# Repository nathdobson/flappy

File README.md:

# A 3d-printed Split Flap Display

This project is a redesign of David
Kingsman's [Split Flap Display](https://www.printables.com/model/69464-split-flap-display). See also the [product page](https://burntoutbakery.shop/).

## How it works

This display shows a sequence of symbols in individual 3d-printed modules. Each module contains a drum with flaps
displaying individual symbols. This is similar to a rolodex, except each symbol is split across the front of one flap
and the back of another flap. A motor rotates the drum to change from one symbol to another.

A client (e.g. [this webpage](https://flappy-7d77d.web.app/www)) sends messages to the microcontroller (MCU)
over [MQTT](https://mqtt.org/), a standardized publish/subscribe message protocol designed for IOT devices. Once the MCU
receives a message, it communicates with a series of daisy-chained motor driver circuit boards on the back of each
module. Each driver contains one shift register for controlling a unipolar stepper motor and one shift register for
reading a digital hall effect sensor. Each motor spins until a magnet on the drum activates the hall sensor, indicating
that the drum is at a particular absolute orientation. The motor then spins a specific number of steps to reach the
desired symbol.

## Prerequisites

Building this project from scratch requires a specific set of equipment and skills.

### Equipment

* Required

    * 3D printer with multi-material support (e.g. Bambu Labs A1 mini with AMS [^2]).
    * Device with a USB port capable of running Chrome.
    * [Soldering iron with temperature adjustment](https://www.amazon.com/Soldering-Digital-Welding-Portable-Electric/dp/B08R3515SF?th=1)
      for assembling boards and pushing Ruthex inserts into 3D printed parts.
    * Wire cutters
    * Wire strippers
    * Pliers
    * Allen wrenches

* Recommended

    * ["Dupont" crimping tool](https://www.amazon.com/IWISS-SN-28B-Crimping-AWG28-18-Dupont/dp/B00OMM4YUY?th=1) for
      assembling cables.
    * Multimeter for basic connection and voltage tests.

* Potentially useful
    * Laptop with at least 32GB of RAM for rendering models.
    * Oscilloscope for debugging serial communications.

### Skills

* Required
    * Soldering through-hole components
    * Crimping custom cables
* Recommended
    * The Rust programming language
    * Basic embedded software development
    * Basic understanding of CAD
    * Basic 3D printing debugging skills
    * Basic digital circuit design

## Bill of Materials

| Name of Part                                                                                                                                                                        | Quantity per display | Quantity per letter | 
|-------------------------------------------------------------------------------------------------------------------------------------------------------------------------------------|----------------------|---------------------|
| [Raspberry Pi Pico 2 W MCU with headers](https://www.adafruit.com/product/6328)                                                                                                     | 1                    |                     |
| 12v power supply (at least 250mA per character)                                                                                                                                     | 1                    |                     |
| [Adafruit 12v to 5v converter](https://www.adafruit.com/product/5882)                                                                                                               | 1                    |                     |
| [Custom motor driver circuit board](https://github.com/nathdobson/flappy/tree/main/driver)                                                                                          |                      | 1                   |
| [28BYJ-48 12v motor](https://www.amazon.com/Podazz-4-Phase-5-Line-Stepper-28BYJ-48/dp/B0DCFV3C2C)                                                                                   |                      | 1                   |
| [KY-003 hall sensor module](https://www.amazon.com/Ransanx-Magnetic-KY-003-3-3V-5V-Pressure/dp/B0F32N1LHX?th=1)                                                                     |                      | 1                   |
| [PLA (background color)](https://us.store.bambulab.com/products/pla-basic-filament)                                                                                                 | ~132 g               | ~217 g              |
| [PLA (foreground/text color)](https://us.store.bambulab.com/products/pla-basic-filament)                                                                                            |                      | ~18 g               |
| [PETG](https://us.store.bambulab.com/products/petg-hf) for stacked prints (optional)                                                                                                |                      | ~30 g               |
| Ruthex M2 inserts                                                                                                                                                                   | 4                    | 8                   |
| Ruthex M3 inserts                                                                                                                                                                   | 4                    | 6 - 8               |
| [M2 x 6mm button head screws](https://www.amazon.com/dp/B0CNQXP56N?th=1)                                                                                                            | 4                    | 6                   |
| [M2 x 10mm button head screws](https://www.amazon.com/dp/B0CNQVP8CC?th=1)                                                                                                           |                      | 2                   |
| [M3 x 6mm button head screws](https://www.amazon.com/dp/B0DNMZWZZV?th=1)                                                                                                            |                      | 6                   |
| [6mm x 2mm disc magnets](https://www.amazon.com/dp/B0CZ71S57Y?ref=ppx_yo2ov_dt_b_fed_asin_title&th=1) for drum                                                                      |                      | 1                   |
| Assorted dupont crimps, housings, and pin headers                                                                                                                                   |                      |                     |
| [26 AWG UL1061 stranded wire](https://www.remingtonindustries.com/hook-up-wire/hook-up-wire-26-awg-ul1061-stranded-kit-2-color-sets-2-spool-sizes-available) for hall sensor cables |                      |                     |
| Assorted solid wire for manually soldered boards                                                                                                                                    |                      |                     |
| Assorted stranded wire for cables                                                                                                                                                   |                      |                     |

## Repository structure

The repository is divided into several hardware and software components:

* [common/](common/) A cargo workspace with utilities and configuration in use by several components
* [driver/](driver/) A KiCad PCB design for the motor driver attached to each character.
* [firmware/](firmware/) A cargo workspace with the firmware for the Raspberry Pi Pico 2 W.
* [models/](models/) A cargo crate with binaries that generate .3mf files for each 3D-printed part.
* [native-client/](native-client/) A cargo workspace with a binary for configuring the display over USB or Bluetooth.
* [spindle/](spindle/) A cargo workspace with a simple scripting language for controlling the display.
* [submodules/](submodules/) A set of git submodules with forks of dependencies.
* [submodules/patina-rs](submodules/patina-rs/) A CAD library for generating 3D meshes from SDFs (signed distance
  functions).
* [web-client](web-client/) A WASM web application for interacting with the display.

## Instructions

### Hardware

1. Download the [latest release](https://github.com/nathdobson/flappy/releases/latest).
1. Order driver PCBs with JLCPCB:
    * `driver-jlcpcb-GERBER.zip` for producing the raw boards.
    * `driver-jlcpcb-BOM.csv` for ordering parts.
    * `driver-jlcpcb-CPL.csv` for placing and assembling parts.
1. For each module, print one each of the following:
    * `model-housing.3mf`: An enclosure for the module.
    * `model-inner.3mf`: The inner half of the drum.
    * `model-outer.3mf`: The outer half of the drum.
    * `model-flaps.3mf`: All flaps, stacked with PETG support. Ensure you have flow ratios tuned correctly for all
      filaments. This is effectively a 100% infill print, so overextrusion will ruin the top flaps. Underextrusion of
      the PLA will result in noticeable gaps. Underextrusion of the PETG support will ruin the surface quality of the
      PLA as it sinks into the gaps.
2. For each display, print one of the following:
    * `model-left-cap.3mf`: The cap for the left side of the display, where the motherboard goes.
    * `model-right-cap.3mf`: The cap for the right side of the display.
1. Press M2 and M3 Ruthex threaded inserts into the prints with a soldering iron.
1. Glue magnets into the inner drums. Ensure magnets are in the appropriate orientation for your sensors.
1. Connect inner and outer drums with screws.
1. Insert flaps into drum. PLA flaps should bend enough to fit in. Aligning the first letter with the magnet will
   simplify later calibration.
1. [Important] Remove the pull-up resistor or pull-up LED from the sensors[^1]. This is easy with flush cutters.
1. Route the motor and sensor cables through housings.
1. Connect all cables.
1. Connect the motors, sensors, and drivers to the housings with M2 and M3 screws. Ensure the motor tabs are properly
   centered on the supports.
1. Press the drum assemblies onto the motor axle. Ensure all flaps are pointed clockwise so they won't jam as the drum
   assembly rotates counter-clockwise.

### Software

1. Set up an MQTT broker (e.g. with https://www.emqx.com/).
1. Install the firmware by loading the [setup tool](https://flappy-7d77d.web.app/www/?tab=setup) in Chrome.
1. Fill out the settings in the setup tool. See [blank.json](native-client/blank.json) for defaults.
1. Enter the MQTT broker details in the [connect tool](https://flappy-7d77d.web.app/www/?tab=setup). You can use the resulting URL to connect to the display.
1. Adjust calibration values until the expected letters appear consistently.

## Controlling the display

### MQTT Protocol

In addition to controlling the display with the website, you may communicate directly with the display over MQTT. Each
display publishes or
subscribes to a set of topics with a common topic prefix.

#### Topic prefix + `"/info"`

The display publishes a `DeviceInfo` message (see [common/protocol/src/setup.rs](common/protocol/src/setup.rs)) on this
topic. This message is retained by the server, so new subscriptions to this topic will immediately receive this message.

#### Topic prefix + `"/request"`

Clients may publish `DisplayRequest` messages (see [common/protocol/src/display.rs](common/protocol/src/display.rs)) on
this
topic. If the display is processing a previous request when a new request arrives, the display cancels the previous
request and starts the new one.

##### `Run` messages

To display a single static message, send a UTF-8 encoded string as follows:

```
{"Run": "helloworld"}
```

The display splits the message into unicode graphemes, then tries to find the best match for each grapheme. The
algorithm accounts for [Unicode Equivalence](https://en.wikipedia.org/wiki/Unicode_equivalence) and capitalization.

##### `RunSpindle` messages

To display a repeating or changing message, send a UTF-8 encoded `spindle` script as follows:

```
{"RunSpindle": "display(\"hi\");sleep_ms(1000);display(\"hi\");"}
```

See the [Spindle](spindle/README.md) documentation for details on the scripting language.

#### Topic prefix + `"/response"`

When the display starts spinning the flaps to a new position, it sends a `Start` message with the content that will
appear. This message may not exactly match the original message due to normalization or capitalization changes.

```
{"Start":["H","E","L","L","O","W","O","R","L","D"]}
```

When the display stops spinning the flaps, it sends an equivalent `Stop` message:

```
{"Stop":["H","E","L","L","O","W","O","R","L","D"]}
```

The stop message is retained, so clients may determine the current contents of the display.

# License
The contents of the [models](models/) and [driver](driver/) directories and associated release artifacts
are licensed under the [CERN-OHL-W license](LICENSE-CERN-OHL-W-2.0). The remainder of this repository
is licensed under the [LGPL v3.0 license](LICENSE-LGPL-3.0).

[^2]: The provided 3MF files are configured for use with BambuStudio and tuned for PLA with PETG support on the Bambu A1 Mini
with AMS. The files will likely work on other slicers and printers, but may require additional tuning.

[^1]: The KY-003 board contains an A3144 digital hall sensor chip. The A3144 has a minimum Vcc of 4.5V and open-collector
active-low digital output. The KY-003 includes a resistor and LED in series to pull-up the output signal to Vcc. This
pull-up means the minimum logic output voltage for the KY-003 is also 4.5V. The
Pico's maximum logic voltage is 3.3V, so it cannot connect to a KY-003 without some extra work. Also, the LED introduces
a
voltage drop, which makes it's use as a pull-up in the first place questionable. Instead, we remove the pull-ups from
the KY-003, provide 12V to Vcc, and add a pull-up resistor to 3.3V on the driver board. Failure to remove the pull-ups
will likely result in damage to the driver boards.

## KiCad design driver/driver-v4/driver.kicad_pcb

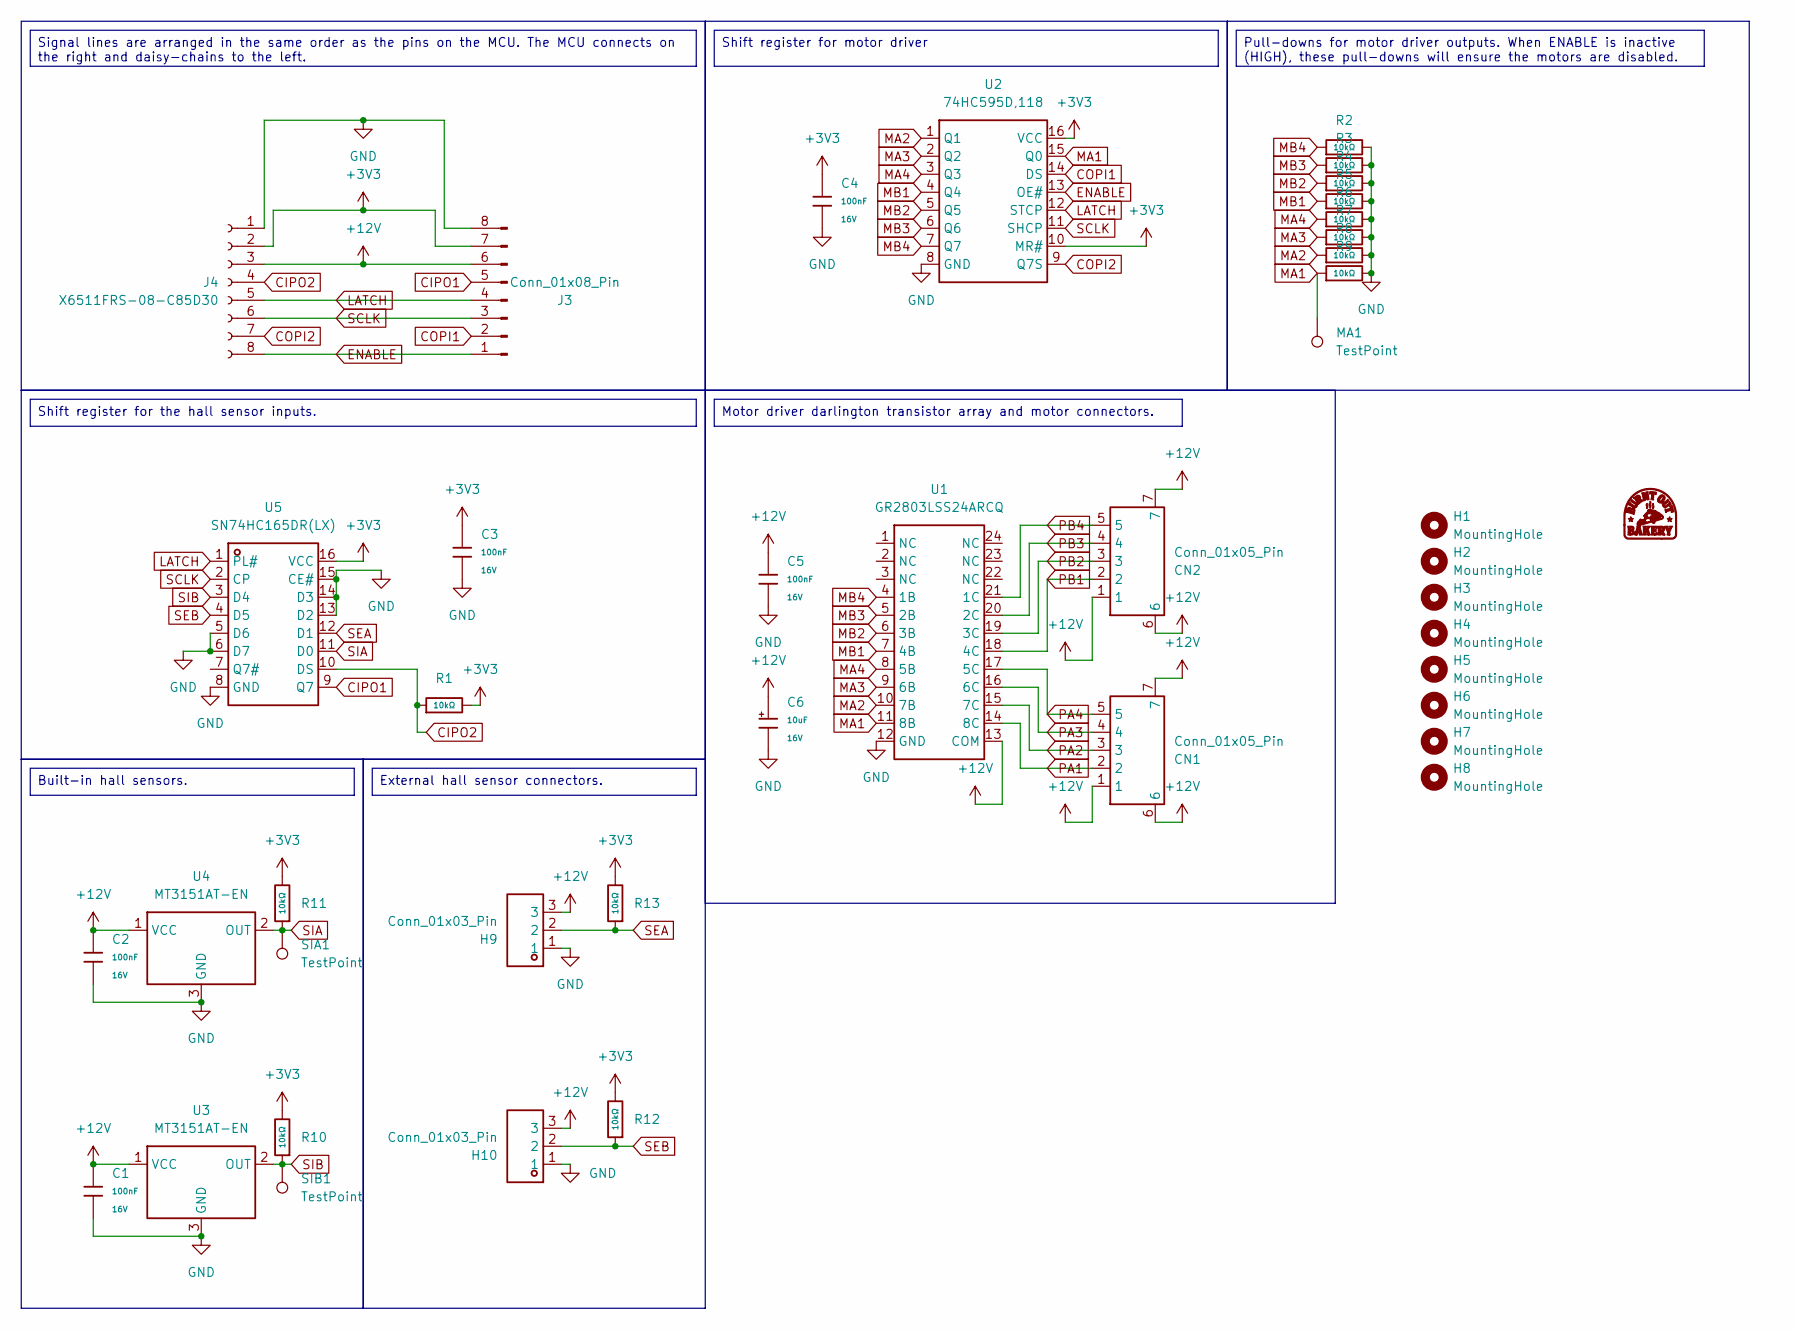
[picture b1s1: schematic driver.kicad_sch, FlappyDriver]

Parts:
C1, C2, C3, C4, C5: 100nF; C_0402; Voltage Rated 16V; Tolerance ±10%; Part CL05B104KO5NNNC; LCSC C1525
C6: 10uF; C_CASE-A-3216-18(mm); Tolerance ±10%; Rated Voltage 16V; Part TAJA106K016RNJ; LCSC C7171
CN1, CN2: Conn_01x05_Pin; CONN-SMD_5P-P2.50_2.54-5P-LT; Manufacturer Part 2.54-5P-LT; LCSC Part Name 1x5P 间距:2.5mm 立贴 系列:XH
G1: LOGO; BurntOutBakery
H1, H2, H3, H4, H5, H6, H7, H8: MountingHole; MountingHole_2.2mm_M2_ISO14580
H9, H10: Conn_01x03_Pin; HDR-TH_3P-P2.54_DZ254S-11-03-48; Manufacturer Part DZ254S-11-03-48; LCSC Part Name 1x3P 间距:2.54mm 方针 立贴
J3: Conn_01x08_Pin; HDR-SMD_PZ254RS-11-08P-01
J4: X6511FRS-08-C85D30; HDR-SMD_8P-P2.54-H-F-L11.5
MA1: TestPoint; TestPoint_THTPad_D2.0mm_Drill1.0mm
R1, R2, R3, R4, R5, R6, R7, R8, R9, R10, R11, R12, R13: 10kΩ; R_0402; Overload Voltage (Max) 50V; Tolerance ±1%; Part 0402WGF1002TCE; LCSC C25744
SIA1: TestPoint; TestPoint_THTPad_D2.0mm_Drill1.0mm
SIB1: TestPoint; TestPoint_THTPad_D2.0mm_Drill1.0mm
U1: GR2803LSS24ARCQ; SSOP-24_L8.7-W3.9-P0.64-LS6.0-BL; Manufacturer Part GR2803LSS24ARCQ; LCSC Part Name 通道数: 8 集射击穿电压: 25V 集电极电流：500mA 最大输入电压：1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
U2: 74HC595D,118; SOIC-16_L9.9-W3.9-P1.27-LS6.0-BL; Manufacturer Part 74HC595D,118; LCSC Part Name 三态输出 串行至串行或并行移位寄存器
U3, U4: MT3151AT-EN; SOT-23-3_L2.9-W1.3-P1.90-LS2.4-BR; Manufacturer Part MT3151AT-EN; LCSC Part Name 单极检测芯片
U5: SN74HC165DR(LX); SOP-16_L10.0-W3.9-P1.27-LS6.0-BL; Manufacturer Part SN74HC165DR(LX); LCSC Part Name 集成电路

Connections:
+3V3: C3.1, C4.1, J3.7, J4.2, R1.2, R10.2, R11.2, R12.2, R13.2, U2.10 (MR#), U2.16 (VCC), U5.16 (VCC)
+12V: C1.1, C2.1, C5.1, C6.1, CN1.1, CN1.6, CN1.7, CN2.1, CN2.6, CN2.7, H9.3, H10.3, J3.6, J4.3, U1.13 (COM), U3.1 (VCC), U4.1 (VCC)
CIPO1: J3.5, U5.9 (Q7)
CIPO2: J4.4, R1.1, U5.10 (DS)
COPI1: J3.2, U2.14 (DS)
COPI2: J4.7, U2.9 (Q7S)
ENABLE: J3.1, J4.8, U2.13 (OE#)
GND: C1.2, C2.2, C3.2, C4.2, C5.2, C6.2, H9.1, H10.1, J3.8, J4.1, R2.2, R3.2, R4.2, R5.2, R6.2, R7.2, R8.2, R9.2, U1.12 (GND), U2.8 (GND), U3.3 (GND), U4.3 (GND), U5.5 (D6), U5.6 (D7), U5.8 (GND), U5.13 (D2), U5.14 (D3), U5.15 (CE#)
LATCH: J3.4, J4.5, U2.12 (STCP), U5.1 (PL#)
MA1: MA1.1, R9.1, U1.11 (8B), U2.15 (Q0)
MA2: R8.1, U1.10 (7B), U2.1 (Q1)
MA3: R7.1, U1.9 (6B), U2.2 (Q2)
MA4: R6.1, U1.8 (5B), U2.3 (Q3)
MB1: R5.1, U1.7 (4B), U2.4 (Q4)
MB2: R4.1, U1.6 (3B), U2.5 (Q5)
MB3: R3.1, U1.5 (2B), U2.6 (Q6)
MB4: R2.1, U1.4 (1B), U2.7 (Q7)
PA1: CN1.2, U1.14 (8C)
PA2: CN1.3, U1.15 (7C)
PA3: CN1.4, U1.16 (6C)
PA4: CN1.5, U1.17 (5C)
PB1: CN2.2, U1.18 (4C)
PB2: CN2.3, U1.19 (3C)
PB3: CN2.4, U1.20 (2C)
PB4: CN2.5, U1.21 (1C)
SCLK: J3.3, J4.6, U2.11 (SHCP), U5.2 (CP)
SEA: H9.2, R13.1, U5.12 (D1)
SEB: H10.2, R12.1, U5.4 (D5)
SIA: R11.1, SIA1.1, U4.2 (OUT), U5.11 (D0)
SIB: R10.1, SIB1.1, U3.2 (OUT), U5.3 (D4)

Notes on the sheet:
Shift register for the hall sensor inputs.
Signal lines are arranged in the same order as the pins on the MCU. The MCU connects on the right and daisy-chains to the left.
Pull-downs for motor driver outputs. When ENABLE is inactive (HIGH), these pull-downs will ensure the motors are disabled.
Built-in hall sensors.
External hall sensor connectors.
Motor driver darlington transistor array and motor connectors.
Shift register for motor driver

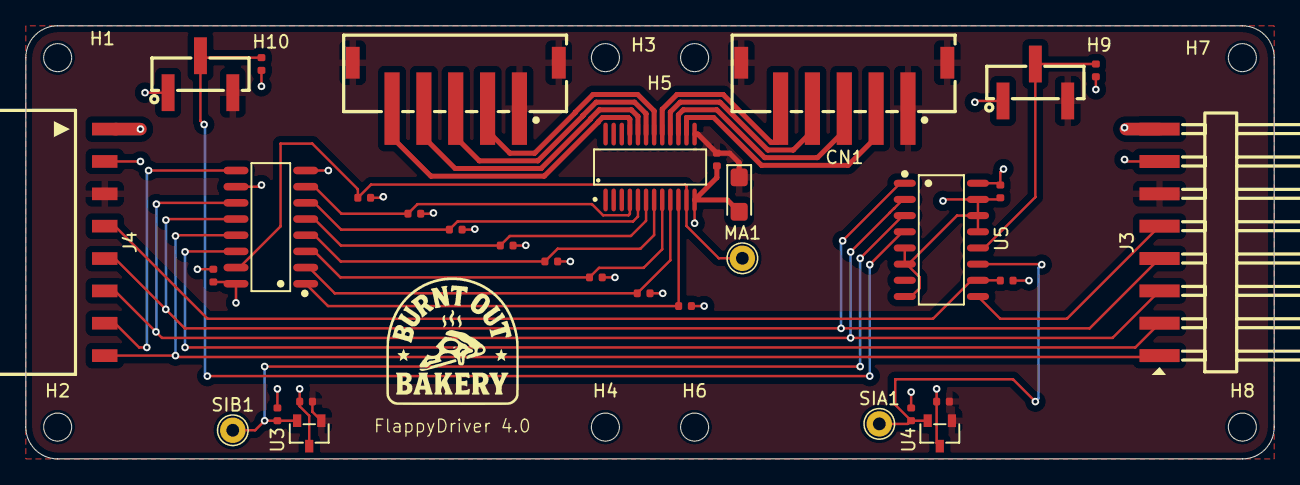
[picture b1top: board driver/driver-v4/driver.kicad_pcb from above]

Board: 4 copper layers, 98.0 x 34.0 mm, 42 parts (0 on the bottom side), 30 nets.

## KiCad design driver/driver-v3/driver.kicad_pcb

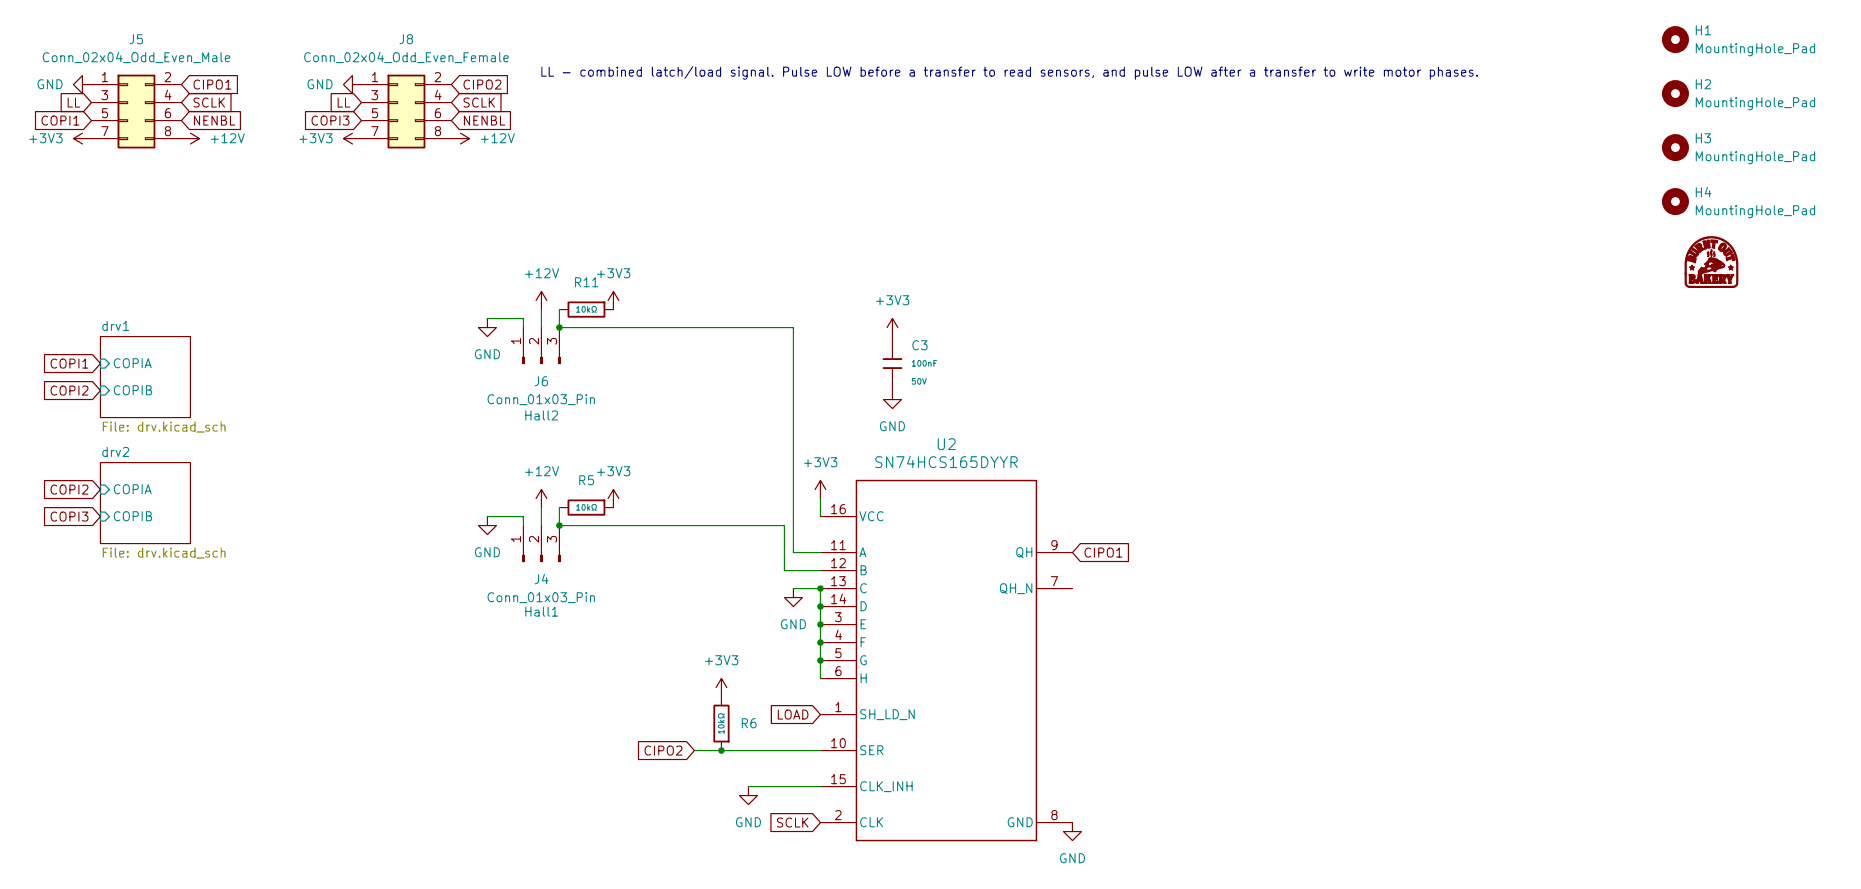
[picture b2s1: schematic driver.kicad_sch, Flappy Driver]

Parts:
C3: 100nF; C_0603; Voltage Rated 50V; Tolerance ±10%; Part CC0603KRX7R9BB104; LCSC C14663
G1: LOGO; BurntOutBakery
H1, H2, H3, H4: MountingHole_Pad; MountingHole_2.2mm_M2_ISO14580
J4, J6: Conn_01x03_Pin; PinHeader_1x03_P2.54mm_Vertical
J5: Conn_02x04_Odd_Even_Male; PinHeader_2x04_P2.54mm_Horizontal
J8: Conn_02x04_Odd_Even_Female; PinSocket_2x04_P2.54mm_Horizontal
R5, R6, R11: 10kΩ; R_0402; Overload Voltage (Max) 50V; Tolerance ±1%; Part 0402WGF1002TCE; LCSC C25744
U2: SN74HCS165DYYR; DYY0016A-MFG

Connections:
+3V3: C3.1, J5.7, J8.7, R5.1, R6.2, R11.1, U2.16 (VCC)
+12V: J4.2, J5.8, J6.2, J8.8; also elsewhere on the board
CIPO1: J5.2, U2.9 (QH)
CIPO2: J8.2, R6.1, U2.10 (SER)
COPI1: J5.5; also elsewhere on the board
COPI3: J8.5; also elsewhere on the board
GND: C3.2, J4.1, J5.1, J6.1, J8.1, U2.3 (E), U2.4 (F), U2.5 (G), U2.6 (H), U2.8 (GND), U2.13 (C), U2.14 (D), U2.15 (CLK_INH); also elsewhere on the board
LL: J5.3, J8.3
LOAD: U2.1 (SH_LD_N)
NENBL: J5.6, J8.6; also elsewhere on the board
unnamed: J4.3, R5.2, U2.12 (B)
unnamed: J6.3, R11.2, U2.11 (A)
SCLK: J5.4, J8.4, U2.2 (CLK); also elsewhere on the board

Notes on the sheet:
LL - combined latch/load signal. Pulse LOW before a transfer to read sensors, and pulse LOW after a transfer to write motor phases.

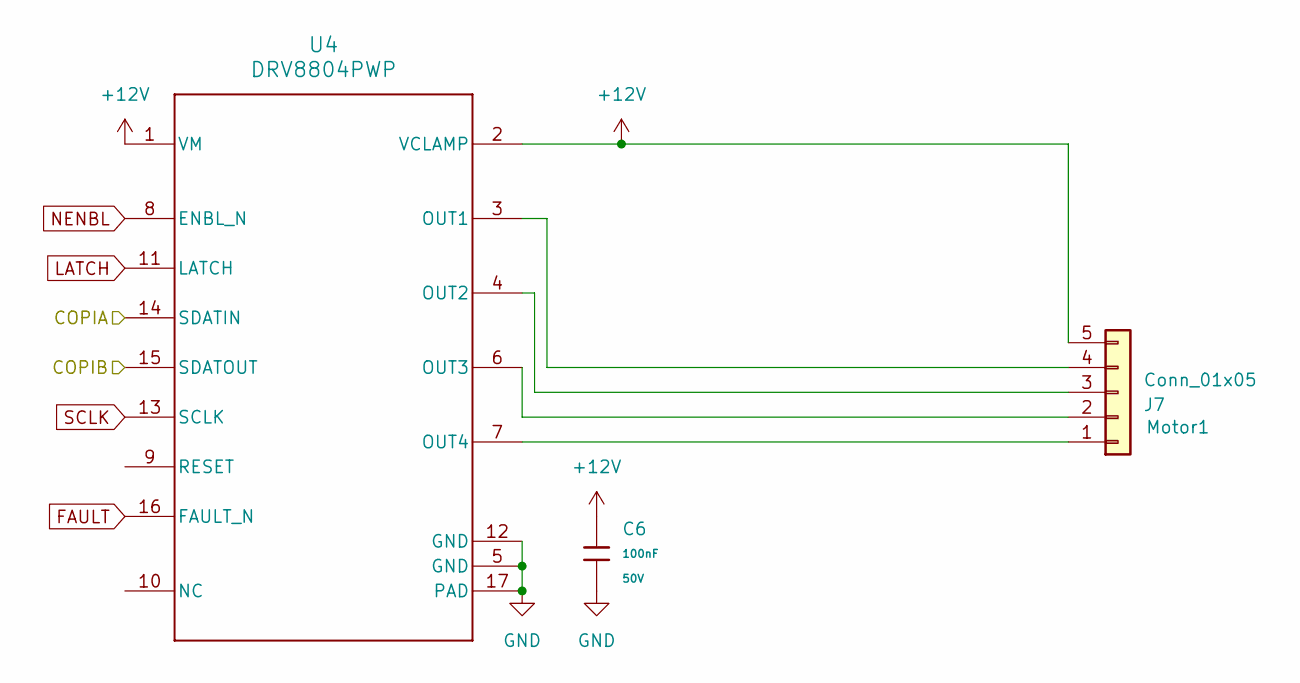
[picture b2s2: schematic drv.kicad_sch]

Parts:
C6: 100nF; C_0603; Voltage Rated 50V; Tolerance ±10%; Part CC0603KRX7R9BB104; LCSC C14663
J7: Conn_01x05; JST_XH_B5B-XH-A_1x05_P2.50mm_Vertical
U4: DRV8804PWP; HTSSOP-16-1EP_4.4x5mm_P0.65mm_EP3.4x5mm_Mask3x3mm_ThermalVi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

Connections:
+12V: C6.1, J7.5, U4.1 (VM), U4.2 (VCLAMP); also elsewhere on the board
COPI1: U4.14 (SDATIN); also elsewhere on the board
COPI2: U4.15 (SDATOUT); also elsewhere on the board
FAULT: U4.16 (FAULT_N); also elsewhere on the board
GND: C6.2, U4.5 (GND), U4.12 (GND), U4.17 (PAD); also elsewhere on the board
LATCH: U4.11 (LATCH); also elsewhere on the board
NENBL: U4.8 (ENBL_N); also elsewhere on the board
unnamed: J7.1, U4.7 (OUT4)
unnamed: J7.2, U4.6 (OUT3)
unnamed: J7.3, U4.4 (OUT2)
unnamed: J7.4, U4.3 (OUT1)
SCLK: U4.13 (SCLK); also elsewhere on the board

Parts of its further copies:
C1: 100nF; C_0603; Voltage Rated 50V; Tolerance ±10%; Part CC0603KRX7R9BB104; LCSC C14663
J3: Conn_01x05; JST_XH_B5B-XH-A_1x05_P2.50mm_Vertical
U1: DRV8804PWP; HTSSOP-16-1EP_4.4x5mm_P0.65mm_EP3.4x5mm_Mask3x3mm_ThermalVi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

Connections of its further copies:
+12V: C1.1, J3.5, U1.1 (VM), U1.2 (VCLAMP); also elsewhere on the board
COPI2: U1.14 (SDATIN); also elsewhere on the board
COPI3: U1.15 (SDATOUT); also elsewhere on the board
FAULT: U1.16 (FAULT_N); also elsewhere on the board
GND: C1.2, U1.5 (GND), U1.12 (GND), U1.17 (PAD); also elsewhere on the board
LATCH: U1.11 (LATCH); also elsewhere on the board
NENBL: U1.8 (ENBL_N); also elsewhere on the board
unnamed: J3.1, U1.7 (OUT4)
unnamed: J3.2, U1.6 (OUT3)
unnamed: J3.3, U1.4 (OUT2)
unnamed: J3.4, U1.3 (OUT1)
SCLK: U1.13 (SCLK); also elsewhere on the board

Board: 2 copper layers, 20 parts (0 on the bottom side), 23 nets, no tracks yet.

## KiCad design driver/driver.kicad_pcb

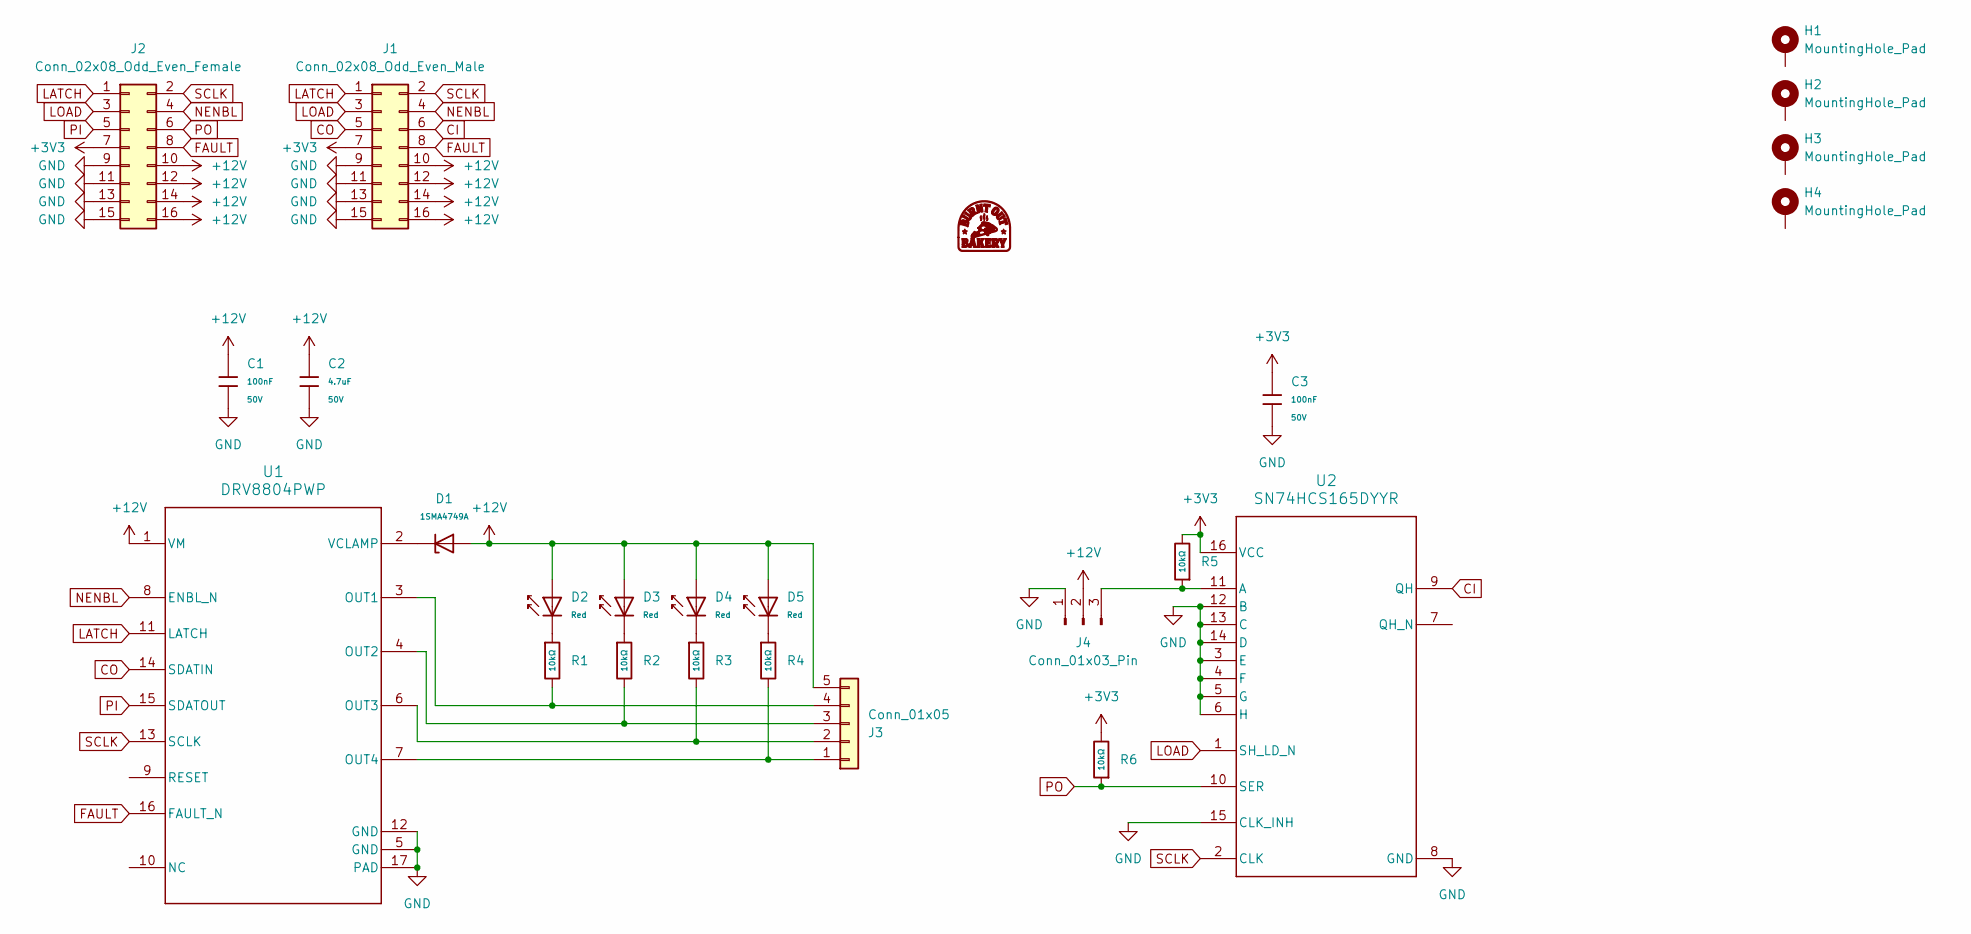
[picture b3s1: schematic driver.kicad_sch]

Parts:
C1, C3: 100nF; C_0603; Voltage Rated 50V; Tolerance ±10%; Part CC0603KRX7R9BB104; LCSC C14663
C2: 4.7uF; C_1206; Voltage Rated 50V; Tolerance ±10%; Part 1206B475K500NT; LCSC C29823
D1: 1SMA4749A; D_DO-214AC(SMA); Part 1SMA4749A; LCSC C19077485
D2, D3, D4, D5: Red; D_0603; Part KT-0603R; LCSC C2286
G1: LOGO; BurntOutBakery
H1, H2, H3, H4: MountingHole_Pad; MountingHole_2.2mm_M2_ISO14580_Pad
J1: Conn_02x08_Odd_Even_Male; PinHeader_2x08_P2.54mm_Horizontal
J2: Conn_02x08_Odd_Even_Female; PinSocket_2x08_P2.54mm_Horizontal
J3: Conn_01x05; JST_XH_B5B-XH-A_1x05_P2.50mm_Vertical
J4: Conn_01x03_Pin; PinHeader_1x03_P2.54mm_Vertical
R1, R2, R3, R4, R5, R6: 10kΩ; R_0402; Overload Voltage (Max) 50V; Tolerance ±1%; Part 0402WGF1002TCE; LCSC C25744
U1: DRV8804PWP; HTSSOP-16-1EP_4.4x5mm_P0.65mm_EP3.4x5mm_Mask3x3mm_ThermalVi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
U2: SN74HCS165DYYR; DYY0016A-MFG

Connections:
+3V3: C3.1, J1.7, J2.7, R5.2, R6.2, U2.16 (VCC)
+12V: C1.1, C2.1, D1.2, D2.2, D3.2, D4.2, D5.2, J1.10, J1.12, J1.14, J1.16, J2.10, J2.12, J2.14, J2.16, J3.5, J4.2, U1.1 (VM)
CI: J1.6, U2.9 (QH)
CO: J1.5, U1.14 (SDATIN)
FAULT: J1.8, J2.8, U1.16 (FAULT_N)
GND: C1.2, C2.2, C3.2, J1.9, J1.11, J1.13, J1.15, J2.9, J2.11, J2.13, J2.15, J4.1, U1.5 (GND), U1.12 (GND), U1.17 (PAD), U2.3 (E), U2.4 (F), U2.5 (G), U2.6 (H), U2.8 (GND), U2.12 (B), U2.13 (C), U2.14 (D), U2.15 (CLK_INH)
LATCH: J1.1, J2.1, U1.11 (LATCH)
LOAD: J1.3, J2.3, U2.1 (SH_LD_N)
NENBL: J1.4, J2.4, U1.8 (ENBL_N)
unnamed: D2.1, R1.1
unnamed: D3.1, R2.1
unnamed: D4.1, R3.1
unnamed: D5.1, R4.1
unnamed: J3.1, R4.2, U1.7 (OUT4)
unnamed: J3.2, R3.2, U1.6 (OUT3)
unnamed: J3.3, R2.2, U1.4 (OUT2)
unnamed: J3.4, R1.2, U1.3 (OUT1)
unnamed: J4.3, R5.1, U2.11 (A)
unnamed: D1.1, U1.2 (VCLAMP)
PI: J2.5, U1.15 (SDATOUT)
PO: J2.6, R6.1, U2.10 (SER)
SCLK: J1.2, J2.2, U1.13 (SCLK), U2.2 (CLK)

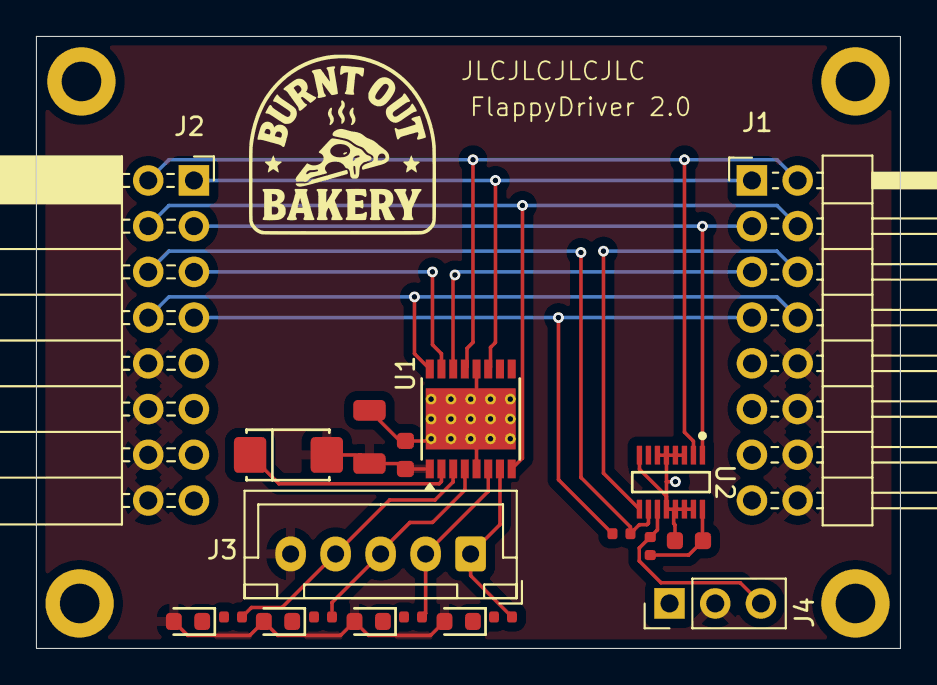
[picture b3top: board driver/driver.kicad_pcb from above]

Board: 2 copper layers, 48.0 x 34.0 mm, 25 parts (0 on the bottom side), 22 nets.

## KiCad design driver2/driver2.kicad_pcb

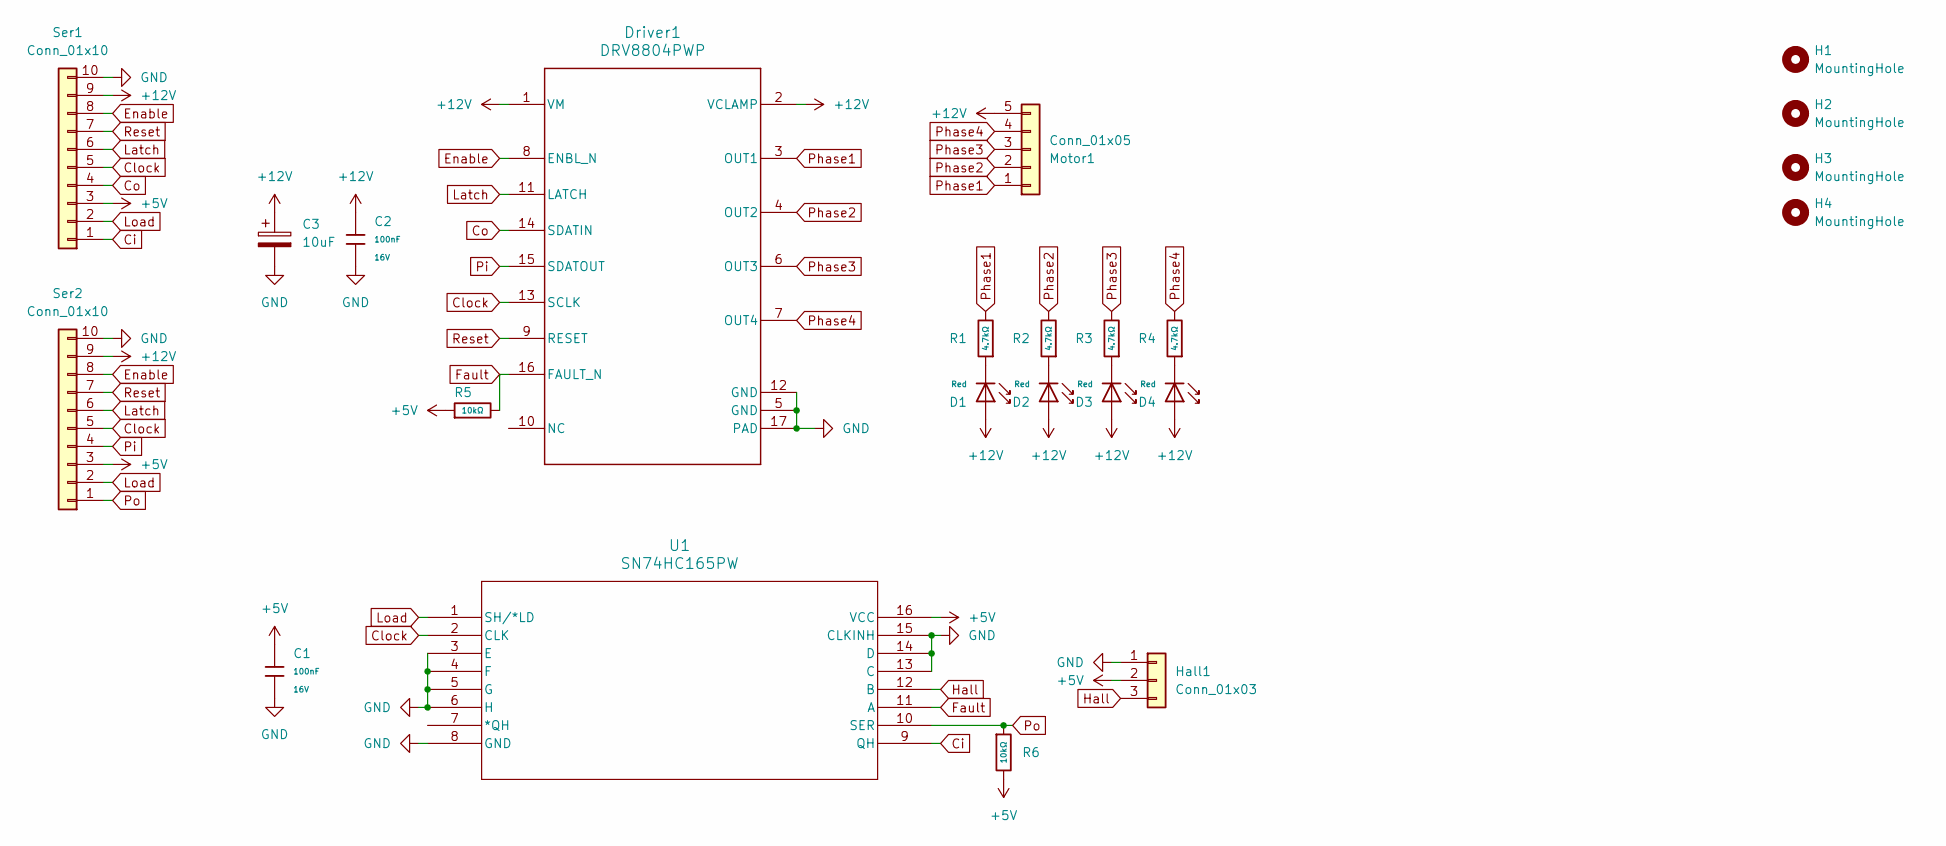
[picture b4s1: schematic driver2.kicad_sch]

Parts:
C1, C2: 100nF; C_0402; Voltage Rated 16V; Tolerance ±10%; Part CL05B104KO5NNNC; LCSC C1525
C3: 10uF; CP_Radial_D5.0mm_P2.00mm
D1, D2, D3, D4: Red; D_0603; Part KT-0603R; LCSC C2286
Driver1: DRV8804PWP; HTSSOP-16-1EP_4.4x5mm_P0.65mm_EP3.4x5mm
H1, H2, H3, H4: MountingHole; MountingHole_2.2mm_M2_Pad_TopBottom
Hall1: Conn_01x03; PinHeader_1x03_P2.54mm_Vertical
Motor1: Conn_01x05; JST_XH_B5B-XH-A_1x05_P2.50mm_Vertical
R1, R2, R3, R4: 4.7kΩ; R_0603; Overload Voltage (Max) 75V; Tolerance ±1%; Part 0603WAF4701T5E; LCSC C23162
R5, R6: 10kΩ; R_0402; Overload Voltage (Max) 50V; Tolerance ±1%; Part 0402WGF1002TCE; LCSC C25744
Ser1, Ser2: Conn_01x10; JST_XA_B10B-XASK-1_1x10_P2.50mm_Vertical
U1: SN74HC165PW; PW16

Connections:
+5V: C1.1, Hall1.2, R5.1, R6.2, Ser1.3, Ser2.3, U1.16 (VCC)
+12V: C2.1, C3.1, D1.2, D2.2, D3.2, D4.2, Driver1.1 (VM), Driver1.2 (VCLAMP), Motor1.5, Ser1.9, Ser2.9
Ci: Ser1.1, U1.9 (QH)
Clock: Driver1.13 (SCLK), Ser1.5, Ser2.5, U1.2 (CLK)
Co: Driver1.14 (SDATIN), Ser1.4
Enable: Driver1.8 (ENBL_N), Ser1.8, Ser2.8
Fault: Driver1.16 (FAULT_N), R5.2, U1.11 (A)
GND: C1.2, C2.2, C3.2, Driver1.5 (GND), Driver1.12 (GND), Driver1.17 (PAD), Hall1.1, Ser1.10, Ser2.10, U1.3 (E), U1.4 (F), U1.5 (G), U1.6 (H), U1.8 (GND), U1.13 (C), U1.14 (D), U1.15 (CLKINH)
Hall: Hall1.3, U1.12 (B)
Latch: Driver1.11 (LATCH), Ser1.6, Ser2.6
Load: Ser1.2, Ser2.2, U1.1 (SH/*LD)
unnamed: D1.1, R1.1
unnamed: D2.1, R2.1
unnamed: D3.1, R3.1
unnamed: D4.1, R4.1
Phase1: Driver1.3 (OUT1), Motor1.1, R1.2
Phase2: Driver1.4 (OUT2), Motor1.2, R2.2
Phase3: Driver1.6 (OUT3), Motor1.3, R3.2
Phase4: Driver1.7 (OUT4), Motor1.4, R4.2
Pi: Driver1.15 (SDATOUT), Ser2.4
Po: R6.1, Ser2.1, U1.10 (SER)
Reset: Driver1.9 (RESET), Ser1.7, Ser2.7

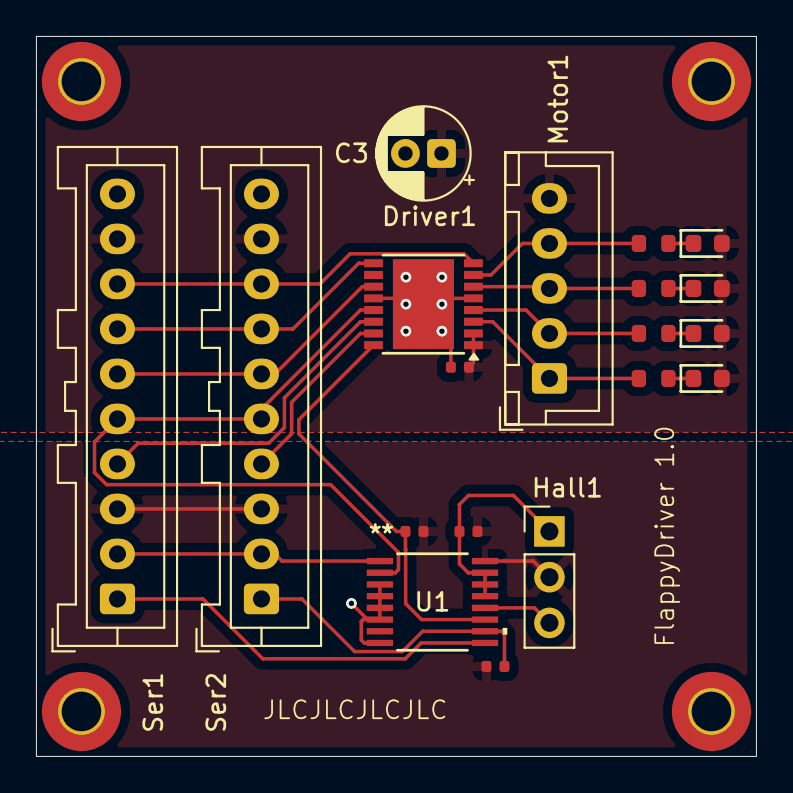
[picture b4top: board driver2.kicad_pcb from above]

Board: 2 copper layers, 40.0 x 40.0 mm, 23 parts (0 on the bottom side), 22 nets.

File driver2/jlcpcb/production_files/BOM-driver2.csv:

Comment,Designator,Footprint,LCSC,Quantity
10uF,C3,CP_Radial_D5.0mm_P2.00mm,C106654,1
DRV8804PWP,Driver1,HTSSOP-16-1EP_4.4x5mm_P0.65mm_EP3.4x5mm,C114176,1
100nF,"C1,C2",C_0402,C1525,2
Conn_01x05,Motor1,JST_XH_B5B-XH-A_1x05_P2.50mm_Vertical,C157991,1
Red,"D1,D2,D3,D4",D_0603,C2286,4
4.7kΩ,"R1,R2,R3,R4",R_0603,C23162,4
10kΩ,"R5,R6",R_0402,C25744,2
Conn_01x03,Hall1,PinHeader_1x03_P2.54mm_Vertical,C2937625,1
Conn_01x10,"Ser1,Ser2",JST_XA_B10B-XASK-1_1x10_P2.50mm_Vertical,C412095,2
SN74HC165PW,U1,PW16,C43420,1
